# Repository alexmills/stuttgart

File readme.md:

# Project Stuttgart

*Last Updated: 11th July 2026*

> Named after the founding location of Bosch in 1886, where a team in 1983 started development of the Connected Area Network.

The goal for this research project is to explore the benefits of having a clearer look at the CAN bus during vehicle diagnostics, instead of relying solely on multimeter or oscilloscope measurements.

## Overview

The tool connects to the CAN bus in a **read only** capacity, receiving messages and monitoring bus health while simultaneously measuring the voltage on the High and Low signal lines to identify physical layer faults. The CAN controller's transmit line is still connected for some future experiments with J1939.

A small web app connects to the tool using WebSerial (in Chrome/Edge) to control and monitor its data output in real time. 

*The design and component selection **will not** take production into consideration, this is purely a research project. I get easily sidetracked worrying about how to make n-amount instead of just making one first...*
## Isolation & Safety

The microcontroller and USB are completely isolated from the components connected to the vehicle electronics through the CAN bus, protecting the laptop and user from any potential voltage differences between chassis ground and mains earth. This isolation also eliminates ground loops, improves signal integrity, and provides a clean ground reference for the vehicle measurements.

## Target Vehicle / Networks

Primary targets are heavy duty vehicles which use a combination of J1939 and J2284 networks. The initial goal of the tool is not to decode these messages but to verify the bus is healthy and that frames are being transmitted without errors or corruption.

Both standards build on ISO 11898 *Road Vehicles - Controller Area Network (CAN),* with their own additions and modifications.

**J1939** spans both **physical** and **application** layers, defining its own physical layer specifications as well as how the messages are structured and what they mean. Unlike J2284, the use of CAN 2.0B 29-bit extended identifiers is mandated.

**J2284** defines the **physical** layer and portions of the **data link** layer, with OBD-II, UDS and proprietary **application** layers running on top. Both standards reference ISO 11898-2 for the high speed CAN physical layer, meaning the bus voltage levels are identical and the same transceiver hardware can be used across all target networks.

## Status

The current state of the project as follows:

- [x] Project Scope
- [x] Architecture & Protocol Design
- [x] Component Selection
- [x] Schematic Design
- [x] PCB Design
- [ ] Enclosure Design (Active)
- [ ] Firmware Implementation (Active)
- [ ] App Implementation (Active)
- [ ] Testing

## Updates 

### 11th July 2026
Order with JLC has been placed! Got stung with extended library part swaps so will need to revise that in the future because it was quite expensive.

## Main Components

| Component              | Part No                       | JLC No    | Status | Models |
| ---------------------- | ----------------------------- | --------- | ------ | ------ |
| MCU                    | Raspberry Pi RP2354A          | C41378174 | ✅      | 📦     |
| CAN FD Controller      | Microchip MCP251863           | C20295647 | ✅      | ✅      |
| Voltage ADC            | MCP3202-CI/SN                 | C56997    | ✅      | ✅      |
| Isolated DC-DC         | TI UCC33420                   | C46461551 | ✅      | ✅      |
| Isolated USB           | TI ISOUSB111DWR               | C5216549  | ✅      | ✅      |
| 3.3V LDO               | OnSemi NCV1117ST33T3G         | C114733   | ✅      | ✅      |
| MCP2518FD Crystal      | Murata XRCGE20M000F3A1AR0     | C6758395  | ✅      | 📦     |
| 12MHz Crystal          | Abracon ABM8-272-T3           | C20625731 | ✅      | ✅      |
| SMPS Inductor          | Abracon AOTA-B201610S3R3-101T | C42411119 | ✅      | ✅      |
| Transceiver TVS Diodes | Littelfuse SMBJ5.0A           | C83333    | ✅      | 📦     |
| ADC Zener Diodes       | Onsemi SZMM5Z3V3T1G           | C464127   | ✅      | 📦     |
| BOOTSEL Button         | Wurth 434133025816            | C5504987  | ✅      | ✅      |
| USB-C Connector        | GCT USB4105-GF-060            | C3025063  | ✅      | 📦     |
| SWD Header             | JST SM03B-SRSS-TB             | C160403   | ✅      | ✅      |
| CANH Socket            | Cliff FCR7350Y (Blue)         | Digikey   | ✅      | ✅      |
| CANL Socket            | Cliff FCR7350G (Green)        | Digikey   | ✅      | ✅      |
| GND Socket             | Cliff FCR7350B (Black)        | Digikey   | ✅      | ✅      |

## System Architecture

Below is the high level architecture of the system, including the USB/Vehicle isolation and main active components.

### Vehicle / USB Isolation

The VBUS from the USB-C connector is isolated using a Texas Instruments UCC33420 DC-DC Converter, providing 1.5W / 300mA to the 5V Rail.

The USB data is isolated using a Texas Instruments ISOUSB111 USB Isolator, which sits between the USB-C Connector and RP2354. Combining this IC with the DC-DC converter means the main components on the PCB sit on the "vehicle side", completely isolated from the USB port and connected computer.

### Vehicle Interface

The CAN communication to the vehicle is achieved using a Microchip MCP251863, integrating the MCP2518-FD Controller and ATA6563 Transceiver into a single package ([Datasheet]([https://ww1.microchip.com/downloads/aemDocuments/documents/OTH/ProductDocuments/DataSheets/External-CAN-FD-Controller-with-SPI-Interface-DS20006027B.pdf](https://ww1.microchip.com/downloads/aemDocuments/documents/APID/ProductDocuments/DataSheets/MCP251863-External-CAN-FD-Controller-with-Integrated-Transceiver-DS20006624.pdf))). The CAN Signals and vehicle reference ground are provided through CLIFF 4mm 1kV "banana" sockets usually found on multimeters, so my normal test leads and accessories can be used.

## Power Requirements

### 3V3 Rail

| Component | Typical  | Max      | Notes             |
| --------- | -------- | -------- | ----------------- |
| RP2354    | 16mA     | 20mA     | USB Comms Test    |
| MCP2518FD | 15mA     | 20mA     | 40MHz SYSCLK      |
| ATA6563   | 0.25mA   | 0.5mA    | VIO 3V3 Logic Pin |
| MCP3202   | 0.4mA    | 0.55mA   | VSS = 5.0V        |
| **TOTAL** | **32mA** | **41mA** |                   |

The RP2354 draws around 16mA with constant data being written to the USB port as per the hardware data sheet. 

### LDO Thermal

The recommended LDO for the RP2354 is the NCP1117 family of which we are using the automotive version, NCV1117

**OnSemi NCP1117**
- Output: 1.0A @ 3.3V
- Maximum Junction Temperature Range: -55c to 150c
- Junction-to-ambient thermal resistance: 160c/W (SOT-223 worst case)

At maximum load of 41mA the LDO dissipates 70mW as heat, causing a junction rise above ambient of only 11c. With a realistic max enclosure temperature of 55c, a junction temperature of 66c is well within limits.

### Isolated 5V Rail

| Condition            | ATA6563    | ISOUSB111 | 5V Direct Total |
| -------------------- | ---------- | --------- | --------------- |
| Startup / No Monitor | 0mA (STBY) | ~12-15mA  | **~12-15mA**    |
| Passive (recessive)  | ~2-5mA     | ~12-15mA  | **~14-20mA**    |
| TX Burst (max dom)   | 70mA       | ~15mA     | **~85mA**       |
| **CANL/H Short**     | **85mA**   | **~15mA** | **~100mA**      |

### Total 5V DC-DC Load

3V3 rail load reflected through the LDO at ~1:1

| Condition             | 3V3 LDO   | 5V Direct  | DC-DC Total | Power @ 5V |
| --------------------- | --------- | ---------- | ----------- | ---------- |
| Startup / No Monitor  | ~32mA     | ~12mA      | ~44mA       | ~220mW     |
| Passive Monitor (max) | ~41mA     | ~17mA      | ~58mA       | ~290mW     |
| TX Burst (max dom)    | ~41mA     | ~85mA      | ~126mA      | ~630mW     |
| **Short Fault (max)** | **~32mA** | **~100mA** | **~141mA**  | **~705mW** |

### DC-DC Converter Thermal

**TI UCC33420**
- 1.5W / 300mA @ 5.0V
- Recommended Junction Temperature Range: -40 to 125c 
- Junction-to-ambient thermal resistance: 59.7c/W
- Dissipation at full load: 1050mW
- Efficiency: ~59%

At the worst case scenario, we draw 141mA or 705mW from the converter which at roughly 59% efficiency requires an input load of 1195mW or 240mA, of which 490mW is dissipated as heat equalling a rise of 29c above ambient. With the realistic max enclosure temperature of 55c, the junction temperature of 84c is well within limits.

For 99% of the time the load is much smaller at around 290mW, requiring 492mW of which 202mW is lost as heat, causing a junction rise above ambient of only 12c. 

### USB Requirements

| Condition             | DC-DC Load     | ISOUSB111 | VBUS Total |
| --------------------- | -------------- | --------- | ---------- |
| Startup / No Monitor  | 74mA / 372mW   | ~12-15mA  | ~89mA      |
| Passive Monitor (max) | 98mA / 492mW   | ~12-15mA  | ~113mA     |
| TX Burst (max dom)    | 213mA / 1068mW | 15mA      | ~228mA     |
| Short Fault (max)     | 240mA / 1195W  | 15mA      | ~256mA     |

With the transceiver in standby mode until needed, our system power requirements at boot are under the 100mA USB initial limit, which can be upped to 400-500mA with negotiations by the RP2354.

## Bus ADC Measurements

The voltage divider for each bus is `R1 = 10kΩ` and `R2 = 47kΩ` so the ratio is calculated as:

```
Vout = Vin x (R2 / (R1 + R2))
Vout = Vin x (47,000 / (10,000 + 47,000))
Vout = Vin x (47,000 / 57,000)
Vout = Vin x 0.8246
```

Below are the estimated values for the ADC measurements at various bus voltages using the above divider with a protection zener diode, clamping at ~3.3V, keeping the ADC within safe limits (3.6V Max). 

| Bus Voltage | ADC Voltage | RAW ADC Value | Notes                         |
| ----------- | ----------- | ------------- | ----------------------------- |
| 0           | 0           | 0             | Bus Dead / Off                |
| 1.5         | 1.237       | 1535          | CAN L Dominant                |
| 2.5         | 2.062       | 2559          | Recessive Idle                |
| 3.5         | 2.886       | 3583          | CAN H Dominant                |
| **3.9**     | **3.223**   | **4000**      | **Clean bus fault threshold** |
| 4.0         | 3.300       | 4095          | Zener Activates               |
| Over 4.0    | 3.300       | 4095          | Clamped - Fault Condition     |

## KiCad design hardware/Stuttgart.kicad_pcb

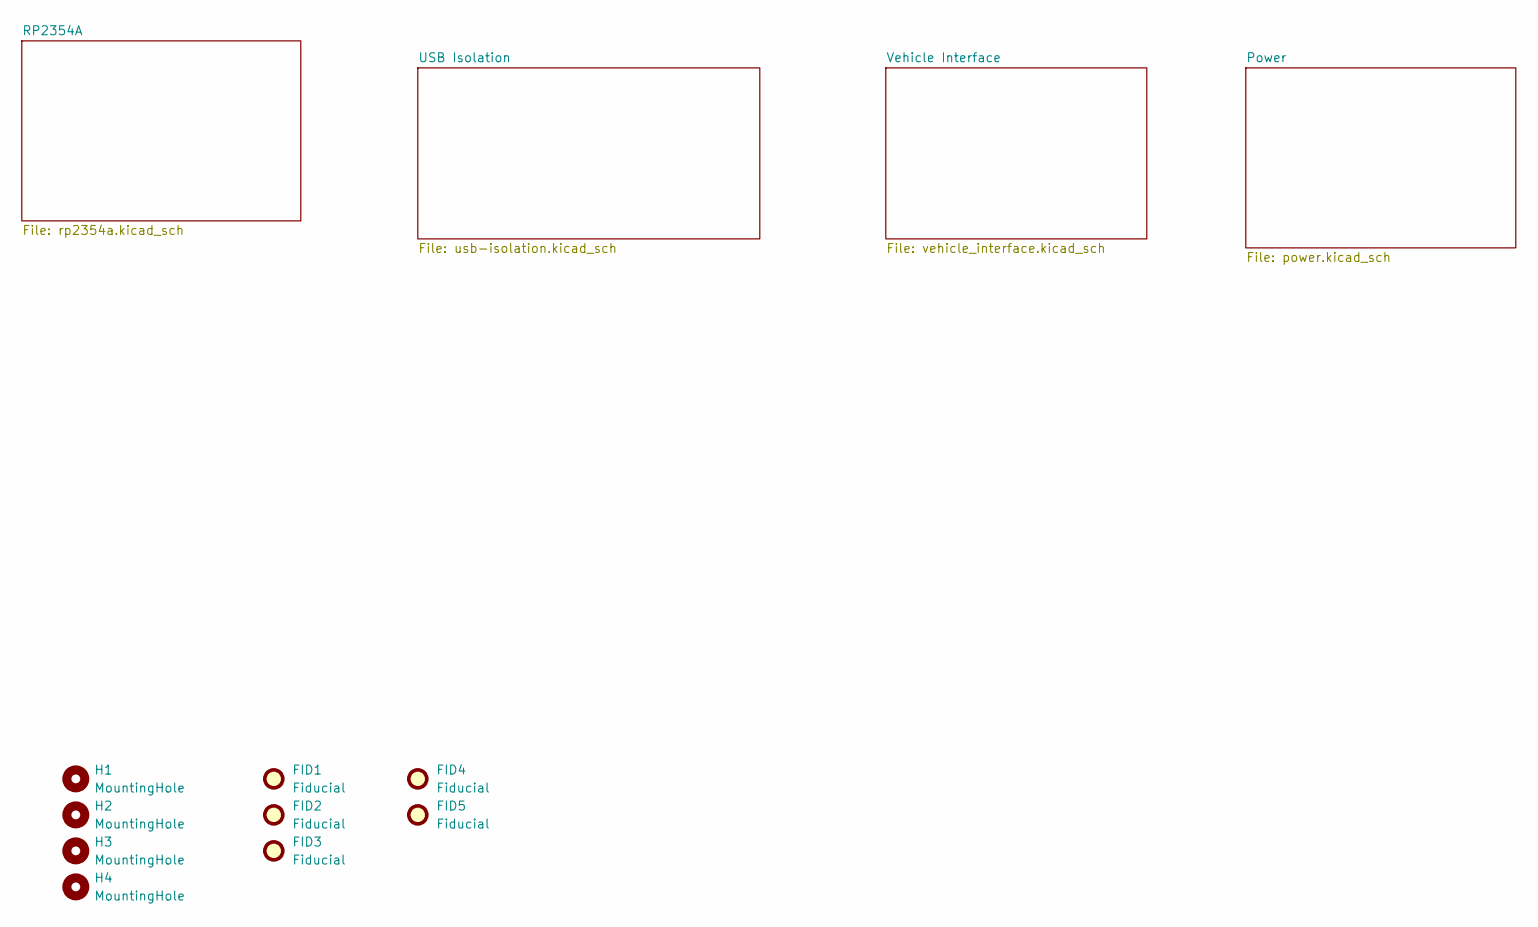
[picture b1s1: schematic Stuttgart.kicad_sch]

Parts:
FID1, FID2, FID3, FID4, FID5: Fiducial; Fiducial_1mm_Mask2mm
H1, H2, H3, H4: MountingHole; MountingHole_3.2mm_M3

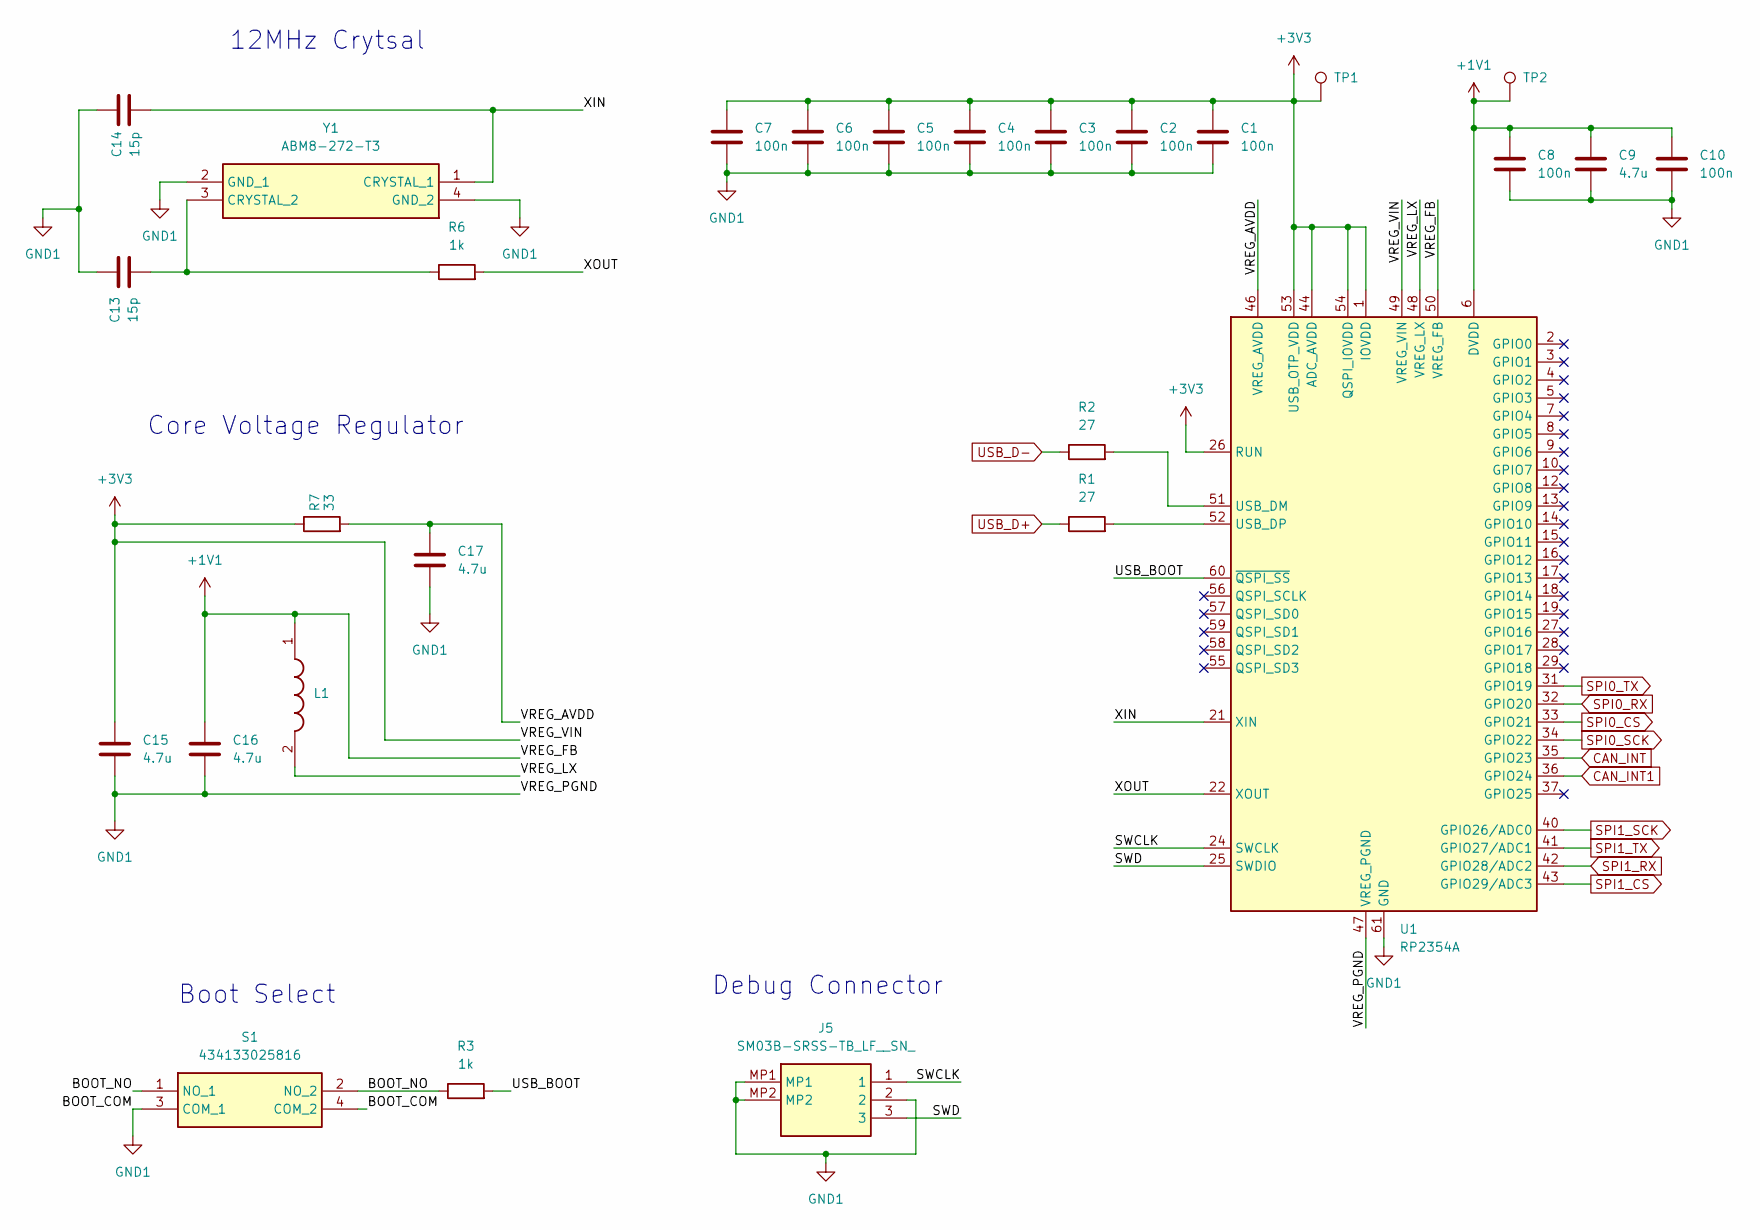
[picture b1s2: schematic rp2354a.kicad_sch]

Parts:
C1, C2, C3, C4, C5, C6, C7, C8, C10: 100n; C_0402_1005Metric
C9, C17: 4.7u; C_0402_1005Metric
C13, C14: 15p; C_0402_1005Metric
C15, C16: 4.7u; C_0402_1005Metric_small_pads
J5: SM03B-SRSS-TB_LF__SN_; SM03BSRSSTBLFSN; Manufacturer_Part_Number SM03B-SRSS-TB(LF)(SN); JLC Part Number C160403
L1: AOTA-B201610S3R3-101-T; AOTAB201610S3R3101T; Mouser Part Number 815-AB201610S3R3101T
R1, R2: 27; R_0402_1005Metric
R3, R6: 1k; R_0402_1005Metric
R7: 33; R_0402_1005Metric
S1: 434133025816; Manufacturer_Part_Number 434133025816; JLC Part Number C5504987
TP1, TP2: TestPoint; TestPoint_Pad_D1.0mm
U1: RP2354A; QFN-60-1EP_7x7mm_P0.4mm_EP3.4x3.4mm; JLC Part Number C41378174
Y1: ABM8-272-T3; ABM8272T3; Mouser Part Number 815-ABM8-272-T3

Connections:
+1V1: C8.1, C9.1, C10.1, C16.1, L1.1, TP2.1 (1_1), U1.6 (DVDD), U1.23 (DVDD), U1.39 (DVDD), U1.50 (VREG_FB)
+3V3: C1.1, C2.1, C3.1, C4.1, C5.1, C6.1, C7.1, C15.1, R7.1, TP1.1 (1_1), U1.1 (IOVDD), U1.11 (IOVDD), U1.20 (IOVDD), U1.26 (RUN), U1.30 (IOVDD), U1.38 (IOVDD), U1.44 (ADC_AVDD), U1.45 (IOVDD), U1.49 (VREG_VIN), U1.53 (USB_OTP_VDD), U1.54 (QSPI_IOVDD); also elsewhere on the board
/RP2354A/BOOT_NO: R3.1, S1.1 (NO_1), S1.2 (NO_2)
/RP2354A/SWCLK: J5.1, U1.24 (SWCLK)
/RP2354A/SWD: J5.3, U1.25 (SWDIO)
/RP2354A/USB_BOOT: R3.2, U1.60 (~QSPI_SS)
/RP2354A/VREG_AVDD: C17.1, R7.2, U1.46 (VREG_AVDD)
/RP2354A/VREG_LX: L1.2, U1.48 (VREG_LX)
/RP2354A/XIN: C14.2, U1.21 (XIN), Y1.1 (CRYSTAL_1)
/RP2354A/XOUT: R6.2, U1.22 (XOUT)
CAN_INT: U1.35 (GPIO23); also elsewhere on the board
CAN_INT1: U1.36 (GPIO24); also elsewhere on the board
GND1: C1.2, C2.2, C3.2, C4.2, C5.2, C6.2, C7.2, C8.2, C9.2, C10.2, C13.2, C14.1, C15.2, C16.2, C17.2, J5.2, J5.MP1, J5.MP2, S1.3 (COM_1), S1.4 (COM_2), U1.47 (VREG_PGND), U1.61 (GND), Y1.2 (GND_1), Y1.4 (GND_2); also elsewhere on the board
unnamed: R2.2, U1.51 (USB_DM)
unnamed: R1.2, U1.52 (USB_DP)
unnamed: C13.1, R6.1, Y1.3 (CRYSTAL_2)
SPI0_CS: U1.33 (GPIO21); also elsewhere on the board
SPI0_RX: U1.32 (GPIO20); also elsewhere on the board
SPI0_SCK: U1.34 (GPIO22); also elsewhere on the board
SPI0_TX: U1.31 (GPIO19); also elsewhere on the board
SPI1_CS: U1.43 (GPIO29/ADC3); also elsewhere on the board
SPI1_RX: U1.42 (GPIO28/ADC2); also elsewhere on the board
SPI1_SCK: U1.40 (GPIO26/ADC0); also elsewhere on the board
SPI1_TX: U1.41 (GPIO27/ADC1); also elsewhere on the board
USB_D+: R1.1; also elsewhere on the board
USB_D-: R2.1; also elsewhere on the board

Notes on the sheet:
Debug Connector
Boot Select
12MHz Crytsal
Core Voltage Regulator

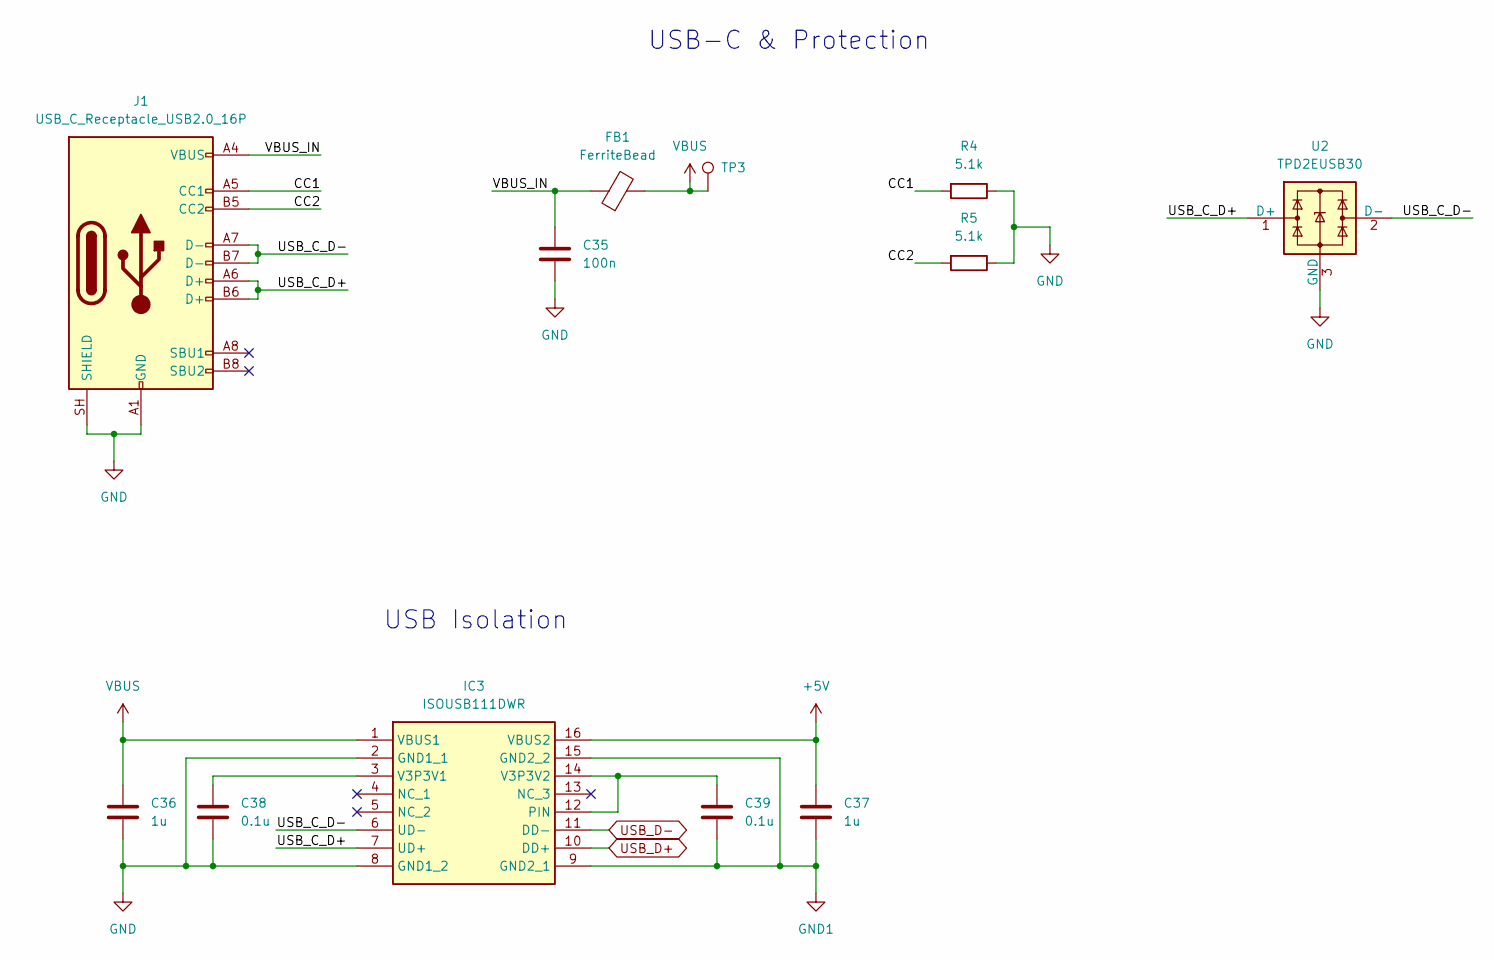
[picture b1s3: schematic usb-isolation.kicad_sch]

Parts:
C35: 100n; C_0603_1608Metric
C36, C37: 1u; C_0603_1608Metric
C38, C39: 0.1u; C_0603_1608Metric
FB1: FerriteBead; L_0603_1608Metric; JLC Part Number C82155
IC3: ISOUSB111DWR; SOIC127P1030X265-16N; Mouser Part Number 595-ISOUSB111DWR
J1: USB_C_Receptacle_USB2.0_16P; USB_C_Receptacle_GCT_USB4105-xx-A_16P_TopMnt_Horizontal; JLC Part Number C3025063
R4, R5: 5.1k; R_0402_1005Metric
TP3: TestPoint; TestPoint_Pad_D1.0mm
U2: TPD2EUSB30; Texas_DRT-3; JLC Part Number C97502

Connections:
+5V: C37.1, IC3.16 (VBUS2); also elsewhere on the board
/USB Isolation/CC1: J1.A5 (CC1), R4.2
/USB Isolation/CC2: J1.B5 (CC2), R5.2
/USB Isolation/USB_C_D+: IC3.7 (UD+), J1.A6 (D+), J1.B6 (D+), U2.1 (D+)
/USB Isolation/USB_C_D-: IC3.6 (UD-), J1.A7 (D-), J1.B7 (D-), U2.2 (D-)
/USB Isolation/VBUS_IN: C35.1, FB1.1, J1.A4 (VBUS), J1.A9 (VBUS), J1.B4 (VBUS), J1.B9 (VBUS)
GND: C35.2, C36.2, C38.2, IC3.2 (GND1_1), IC3.8 (GND1_2), J1.A1 (GND), J1.A12 (GND), J1.B1 (GND), J1.B12 (GND), J1.SH (SHIELD), R4.1, R5.1, U2.3 (GND); also elsewhere on the board
GND1: C37.2, C39.2, IC3.9 (GND2_1), IC3.15 (GND2_2); also elsewhere on the board
unnamed: C39.1, IC3.12 (PIN), IC3.14 (V3P3V2)
unnamed: C38.1, IC3.3 (V3P3V1)
USB_D+: IC3.10 (DD+); also elsewhere on the board
USB_D-: IC3.11 (DD-); also elsewhere on the board
VBUS: C36.1, FB1.2, IC3.1 (VBUS1), TP3.1 (1_1); also elsewhere on the board

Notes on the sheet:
USB Isolation
USB-C & Protection

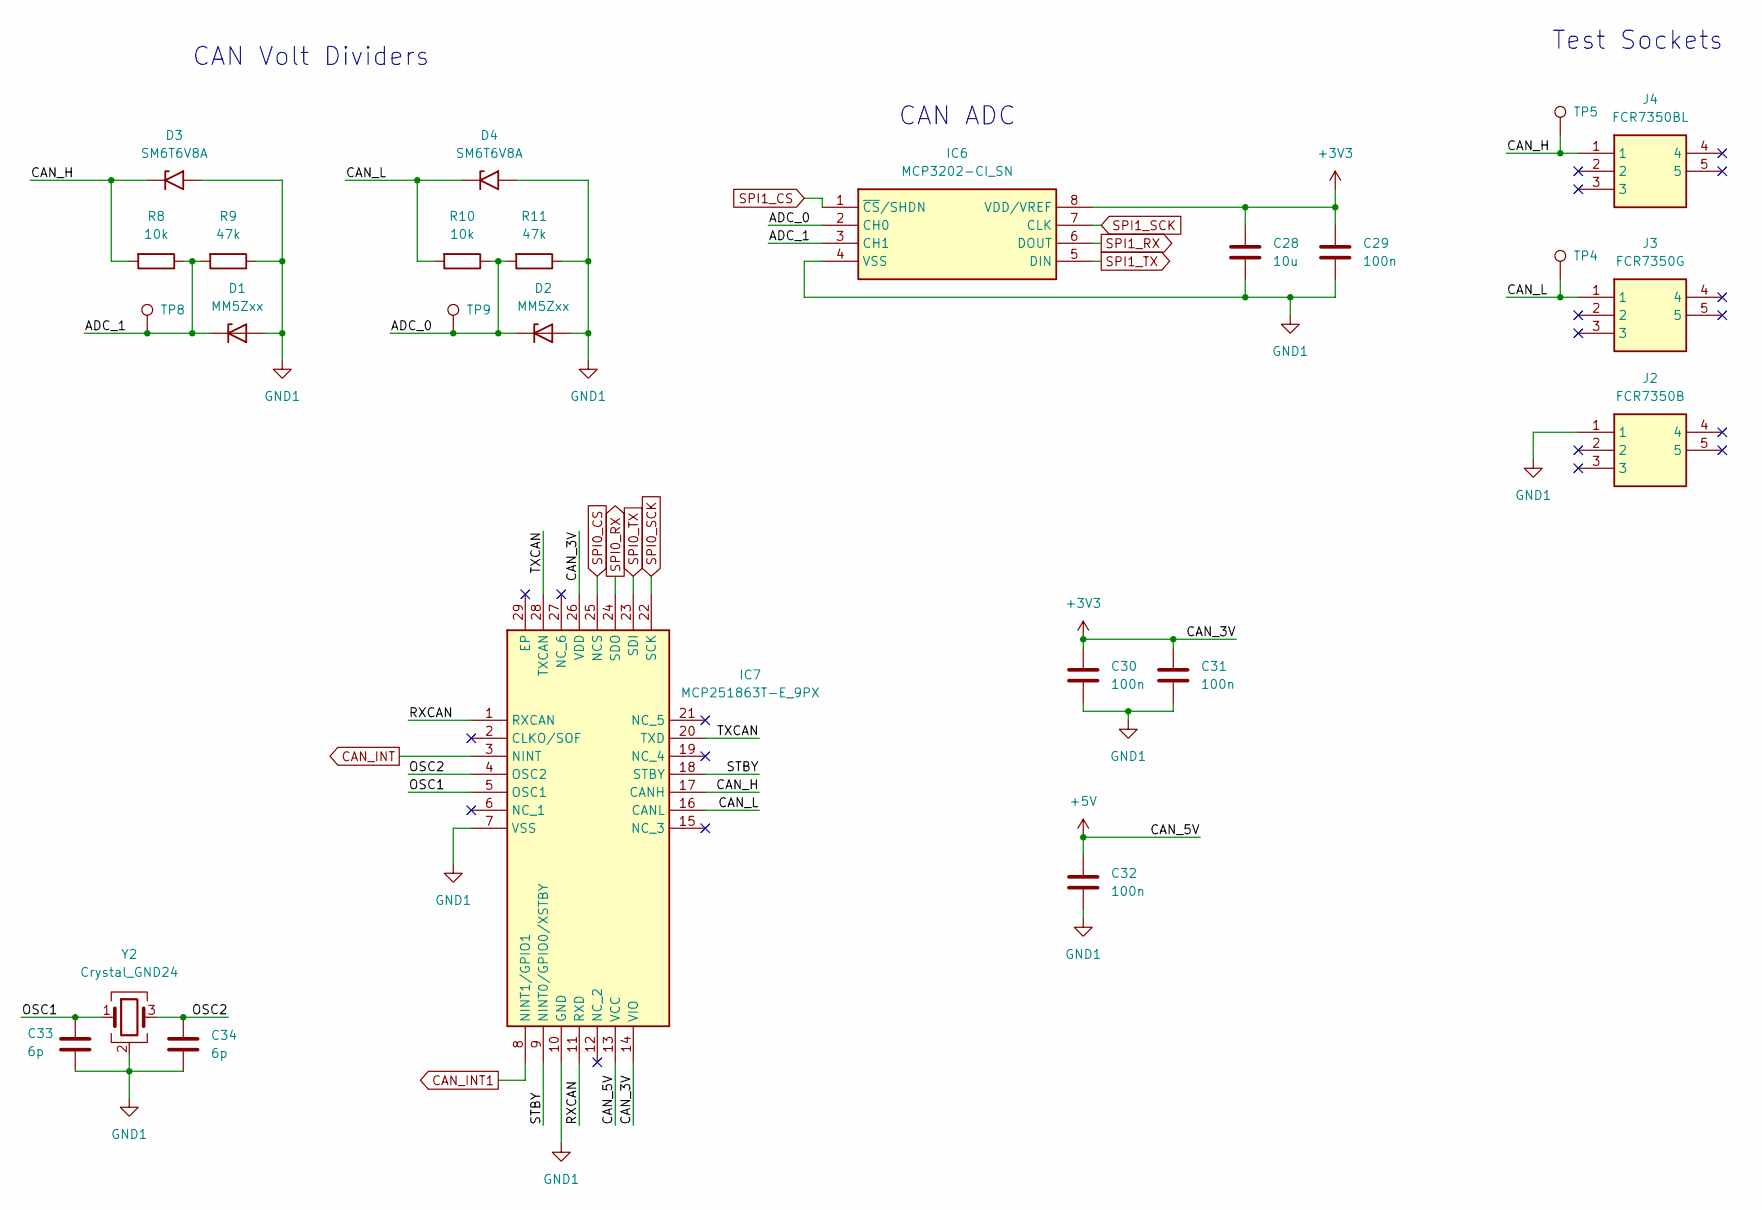
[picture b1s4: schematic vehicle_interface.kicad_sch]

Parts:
C28: 10u; C_0603_1608Metric
C29, C30, C31: 100n; C_0402_1005Metric
C32: 100n; C_0603_1608Metric
C33, C34: 6p; C_0402_1005Metric
D1, D2: MM5Zxx; D_SOD-523; JLC Part Number C464127
D3, D4: SM6T6V8A; D_SMB; JLC Part Number C83333
IC6: MCP3202-CI_SN; SOIC127P600X175-8N; Mouser Part Number 579-MCP3202-CI/SN
IC7: MCP251863T-E_9PX; QFN50P500X500X90-29N-D; Mouser Part Number 579-MCP251863T-E/9PX
J2: FCR7350B; FCR7350G; Manufacturer_Part_Number FCR7350G
J3: FCR7350G; Manufacturer_Part_Number FCR7350G
J4: FCR7350BL; FCR7350G; Manufacturer_Part_Number FCR7350G
R8, R10: 10k; R_0402_1005Metric
R9, R11: 47k; R_0402_1005Metric
TP4, TP5, TP8, TP9: TestPoint; TestPoint_Pad_D1.0mm
Y2: Crystal_GND24; Crystal_SMD_2016-4Pin_2.0x1.6mm; JLC Part Number C6758395

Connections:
+3V3: C28.1, C29.1, C30.1, C31.1, IC6.8 (VDD/VREF), IC7.14 (VIO), IC7.26 (VDD); also elsewhere on the board
+5V: C32.1, IC7.13 (VCC); also elsewhere on the board
/Vehicle Interface/ADC_0: D2.1 (K), IC6.2 (CH0), R10.1, R11.2, TP9.1 (1_1)
/Vehicle Interface/ADC_1: D1.1 (K), IC6.3 (CH1), R8.1, R9.2, TP8.1 (1_1)
/Vehicle Interface/CAN_H: D3.1 (A1), IC7.17 (CANH), J4.1 (1_1), R8.2, TP5.1 (1_1)
/Vehicle Interface/CAN_L: D4.1 (A1), IC7.16 (CANL), J3.1 (1_1), R10.2, TP4.1 (1_1)
/Vehicle Interface/OSC1: C33.1, IC7.5 (OSC1), Y2.1
/Vehicle Interface/OSC2: C34.1, IC7.4 (OSC2), Y2.3
/Vehicle Interface/RXCAN: IC7.1 (RXCAN), IC7.11 (RXD)
/Vehicle Interface/STBY: IC7.9 (NINT0/GPIO0/XSTBY), IC7.18 (STBY)
/Vehicle Interface/TXCAN: IC7.20 (TXD), IC7.28 (TXCAN)
CAN_INT: IC7.3 (NINT); also elsewhere on the board
CAN_INT1: IC7.8 (NINT1/GPIO1); also elsewhere on the board
GND1: C28.2, C29.2, C30.2, C31.2, C32.2, C33.2, C34.2, D1.2 (A), D2.2 (A), D3.2 (A2), D4.2 (A2), IC6.4 (VSS), IC7.7 (VSS), IC7.10 (GND), J2.1 (1_1), R9.1, R11.1, Y2.2 (G), Y2.4 (G); also elsewhere on the board
SPI0_CS: IC7.25 (NCS); also elsewhere on the board
SPI0_RX: IC7.24 (SDO); also elsewhere on the board
SPI0_SCK: IC7.22 (SCK); also elsewhere on the board
SPI0_TX: IC7.23 (SDI); also elsewhere on the board
SPI1_CS: IC6.1 (~CS/SHDN); also elsewhere on the board
SPI1_RX: IC6.6 (DOUT); also elsewhere on the board
SPI1_SCK: IC6.7 (CLK); also elsewhere on the board
SPI1_TX: IC6.5 (DIN); also elsewhere on the board

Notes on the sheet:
CAN ADC
Test Sockets
CAN Volt Dividers

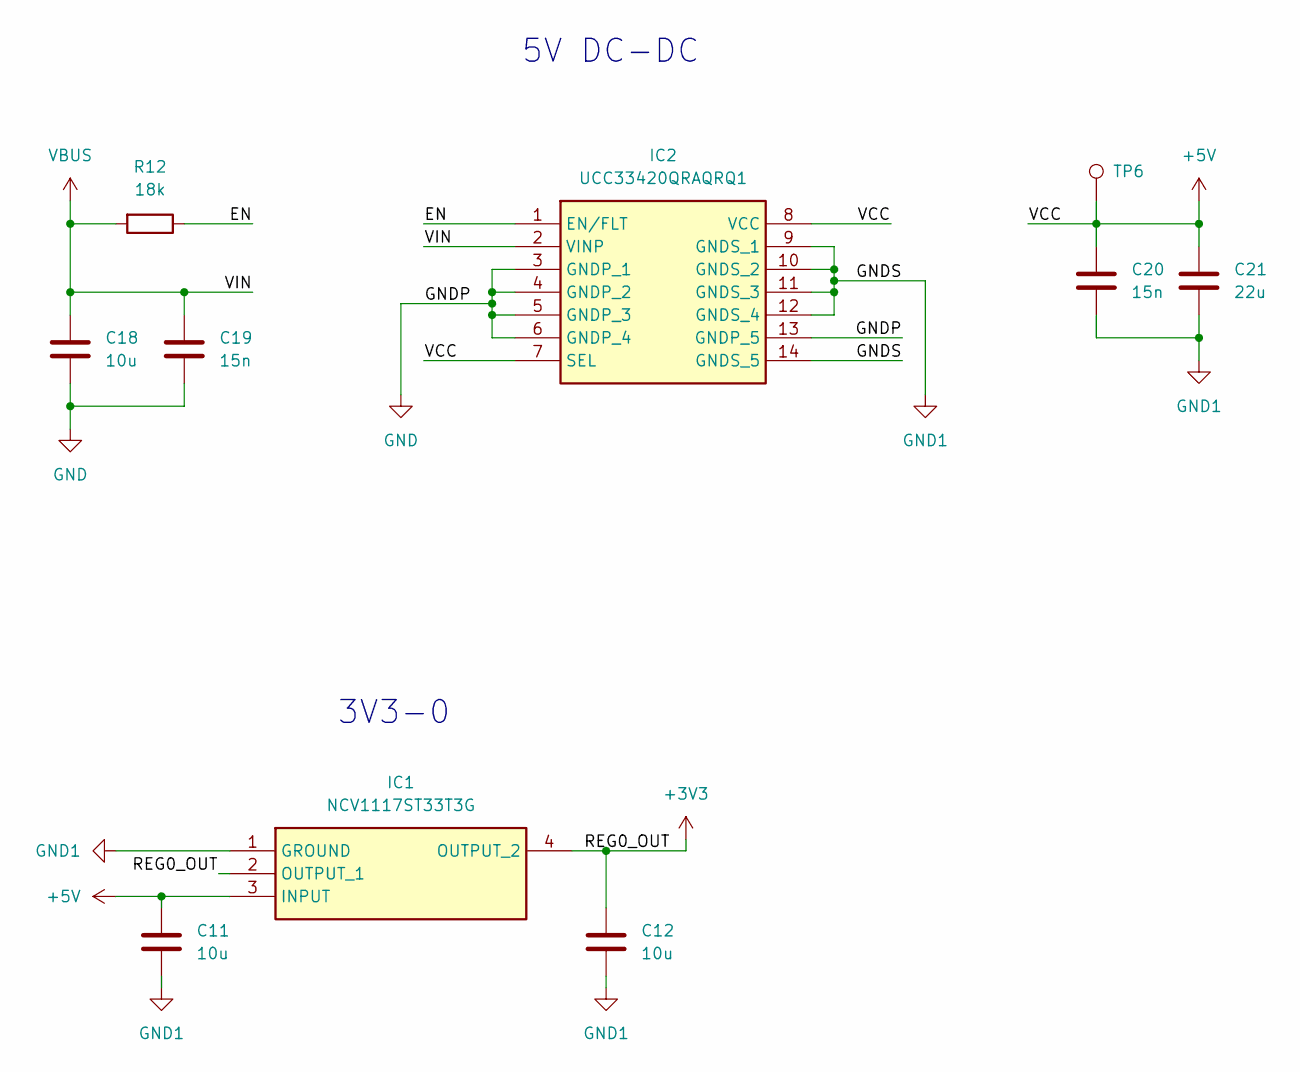
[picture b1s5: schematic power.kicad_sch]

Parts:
C11, C12, C18: 10u; C_0805_2012Metric
C19, C20: 15n; C_0402_1005Metric
C21: 22u; C_0805_2012Metric
IC1: NCV1117ST33T3G; SOT230P700X180-4N; Mouser Part Number 863-NCV1117ST33T3G
IC2: UCC33420QRAQRQ1; UCC33020QRAQRQ1; Mouser Part Number 595-UCC33420QRAQRQ1
R12: 18k; R_0402_1005Metric
TP6: TestPoint; TestPoint_Pad_D1.0mm

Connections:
+3V3: C12.1, IC1.2 (OUTPUT_1), IC1.4 (OUTPUT_2); also elsewhere on the board
+5V: C11.1, C20.1, C21.1, IC1.3 (INPUT), IC2.7 (SEL), IC2.8 (VCC), TP6.1 (1_1); also elsewhere on the board
/Power/EN: IC2.1 (EN/FLT), R12.1
GND: C18.2, C19.2, IC2.3 (GNDP_1), IC2.4 (GNDP_2), IC2.5 (GNDP_3), IC2.6 (GNDP_4), IC2.13 (GNDP_5); also elsewhere on the board
GND1: C11.2, C12.2, C20.2, C21.2, IC1.1 (GROUND), IC2.9 (GNDS_1), IC2.10 (GNDS_2), IC2.11 (GNDS_3), IC2.12 (GNDS_4), IC2.14 (GNDS_5); also elsewhere on the board
VBUS: C18.1, C19.1, IC2.2 (VINP), R12.2; also elsewhere on the board

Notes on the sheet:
3V3-0
5V DC-DC

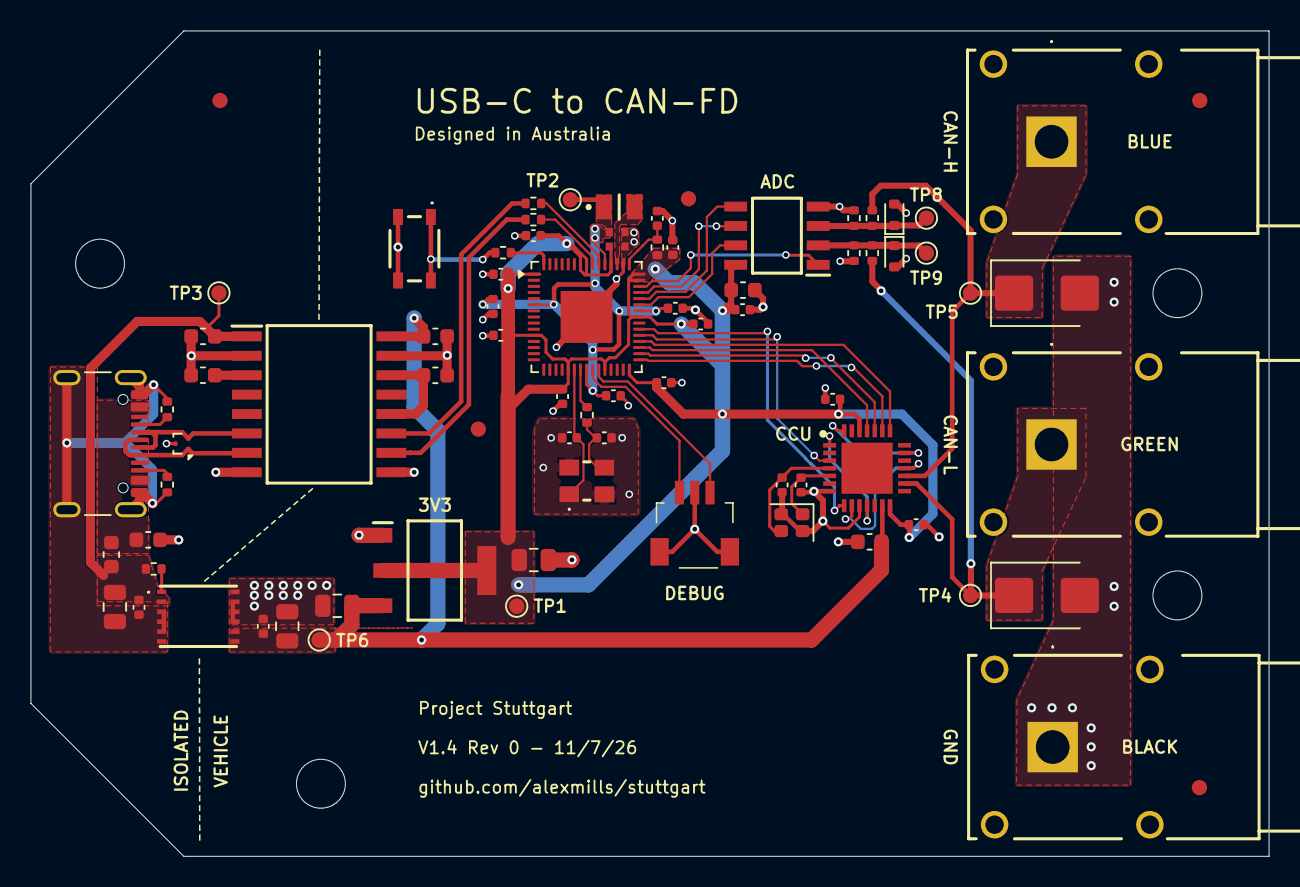
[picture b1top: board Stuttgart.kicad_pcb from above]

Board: 2 copper layers, 81.0 x 54.0 mm, 83 parts (0 on the bottom side), 46 nets.

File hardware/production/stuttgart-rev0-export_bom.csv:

Designator,Footprint,Quantity,Value,LCSC Part #
"C1, C10, C2, C29, C3, C30, C31, C4, C5, C6, C7, C8",0402,12,100n,
"C11, C12, C18",0805,3,10u,
"C13, C14",0402,2,15p,
"C15, C16, C17, C9",0402,4,4.7u,
"C19, C20",0402,2,15n,
C21,0805,1,22u,
C28,0603,1,10u,
"C32, C35",0603,2,100n,
"C33, C34",0402,2,6p,
"C36, C37",0603,2,1u,
"C38, C39",0603,2,0.1u,
"D1, D2",D_SOD-523,2,MM5Zxx,
"D3, D4",D_SMB,2,SM6T6V8A,
FB1,0603,1,FerriteBead,
IC1,SOT230P700X180-4N,1,NCV1117ST33T3G,
IC2,UCC33020QRAQRQ1,1,UCC33420QRAQRQ1,
IC3,SOIC127P1030X265-16N,1,ISOUSB111DWR,
IC6,SOIC127P600X175-8N,1,MCP3202-CI_SN,
IC7,QFN50P500X500X90-29N-D,1,MCP251863T-E_9PX,
J1,USB_C_Receptacle_GCT_USB4105-xx-A_16P_TopMnt_Horizontal,1,USB_C_Receptacle_USB2.0_16P,
J5,SM03BSRSSTBLFSN,1,SM03B-SRSS-TB_LF__SN_,
L1,AOTAB201610S3R3101T,1,AOTA-B201610S3R3-101-T,
"R1, R2",0402,2,27,
"R10, R8",0402,2,10k,
"R11, R9",0402,2,47k,
R12,0402,1,18k,
"R3, R6",0402,2,1k,
"R4, R5",0402,2,5.1k,
R7,0402,1,33,
S1,434133025816,1,434133025816,
U1,QFN-60-1EP_7x7mm_P0.4mm_EP3.4x3.4mm,1,RP2354A,
U2,Texas_DRT-3,1,TPD2EUSB30,
Y1,ABM8272T3,1,ABM8-272-T3,
Y2,Crystal_SMD_2016-4Pin_2.0x1.6mm,1,Crystal_GND24,

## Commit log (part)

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2026-04-21 Base project with Pico and CAN Controller
2026-05-23 Revert "Base project with Pico and CAN Controller"
    This reverts commit e5296eb5b1981e33b805241d96949a49cbd533ba.
2026-05-23 Added project website page as readme
2026-05-23 Working through component selection and JLC matching
2026-05-29 Further component selection
2026-05-31 Updated readme with system architecture
2026-05-31 Link fix?
2026-05-31 Component selection completed
2026-05-31 Base project with additional component symbols and footprints
2026-05-31 Better content management
2026-06-01 Initial batch of components from the minimal-bom example
2026-06-01 Most RP components on board. Core regulator wired up
2026-06-02 Wired in RP Crystal
2026-06-05 Further RP development - Kicad keeps crashing
2026-06-06 Core RP pad work complete
2026-06-06 Boot select button added
2026-06-07 Added DCDC IC
2026-06-08 Added 3V3-1 LDO
2026-06-08 Moved to CAN FD Controller with integrated transceiver
2026-06-08 Link fix
2026-06-08 Table fix
2026-06-09 Further ISO bridge development
2026-06-11 Isolation bridges complete
2026-06-11 CAN ADC on the board
2026-06-12 Further CAN IC work before reworking SPI bridges
2026-06-13 Left hand layout and USB power complete
2026-06-14 Updated readme with new components and layout
2026-06-14 Further CAN controller development
2026-06-17 Schematic nearly complete. Board size finalised.
2026-06-21 Completed ADC, new components and test points
2026-06-23 Prep for new Isolation concept
